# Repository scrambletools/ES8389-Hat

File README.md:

# Scramble Hat-trik — ES8389 Audio Codec HAT

A compact 4-layer audio I/O HAT that stacks on a Waveshare **ESP32-P4** carrier and
gives it a studio-style balanced input and a headset/line output, bridged to the host
over **I²S** (audio) and **I²C** (control). Its headline trick: it taps the carrier's
**802.3 PoE** rail to generate switchable **~48 V-class phantom power** for condenser
microphones — no separate supply.

> **Target carrier:** a Waveshare ESP32-P4-ETH board with PoE module. You will need to solder taps on the output of the bridge rectifiers of the PoE module and connect those wires to J5 on the hat.

---

## Capabilities

- **Balanced analog input** — Neutrik **XLR / ¼″ (6.35 mm) combo** jack (J1) into the
  ES8389 ADC, with input coupling and ESD protection.
- **PoE-tapped phantom power** — ~48 V phantom (tracks the 46–57 V PoE rail) through the
  standard 6.81 kΩ feed pair, **manually switched** (SW1) and **opto-isolated**, with a
  **white presence LED**, a resettable polyfuse, and a TVS rail clamp.
- **Headset / line output** — 3.5 mm **TRRS** jack (J2): stereo output from the DAC plus
  an **electret mic-bias** input path.
- **Stereo audio codec** — Everest **ES8389** (QFN-24): I²S/PCM audio + I²C control.
- **Clean analog power** — ultra-low-noise LDO (TPS7A2033) and ferrite-isolated AVDD.
- **Isolation barrier** — the phantom / XLR side (PGND) is kept separate from the carrier
  audio ground (AGND), bridged only by a **2.2 nF Y2 safety cap** (C19), with a DNP 0 Ω
  ground-lift option (R14).
- **External display header** — 4-pin **I²C** breakout (J6: 3V3 / GND / SDA / SCL) for an
  off-board display.
- **Manufacturable** — JLCPCB gerbers, drills, BOM and placement files are checked in;
  most parts are machine-assembled.

## Signal & power flow

```
  XLR / 6.35" combo (J1) ──coupling──▶ ES8389 ADC ──▶ I²S ──▶ ESP32-P4 carrier
         ▲ phantom
  PoE (J5) ─F1─▶ SW1 ─opto OK1─▶ P-FET Q1 ─▶ 6.81k feed ─▶ XLR pins 2 & 3

  ESP32-P4 carrier ──▶ I²S ──▶ ES8389 DAC ──coupling──▶ TRRS out (J2)
  ESP32-P4 carrier ◀──▶ I²C ◀──▶ ES8389        (+ external display header J6)
```

## Connectors & controls

| Ref | Part | Function |
|---|---|---|
| **J1** | Neutrik NCJ6FA-H | XLR / ¼″ combo — balanced mic/line **input**; ¼″ side is a Hi-Z **instrument input** with auto-detect *(hand-solder)* |
| **J2** | CUI SJ-3524 TRRS | 3.5 mm headset — stereo **output** + electret mic *(hand-solder)* |
| **J3, J4** | 1×7 sockets (8.5 mm) | mezzanine to the carrier — I²S, I²C, power |
| **J5** | 1×2 header | **PoE** rail input from the carrier's PoE module *(hand-solder)* |
| **J6** | 1×4 header | external **I²C** display (3V3 / GND / SDA / SCL) — *DNP; hand-fit (top side) only for a display harness. Eurorack builds don't need it: the interposer drives the display directly* |
| **SW1** | SPDT slide | **phantom power** on/off (manual) — *DNP; populate only in builds that use phantom.* Unpopulated = phantom permanently off; for switchless always-on phantom, bridge SW1 pads 1–2 instead |

## Key components

| Ref | Part | Role |
|---|---|---|
| **U1** | Everest ES8389 (QFN-24) | stereo audio codec |
| **U2** | TI TPS7A2033 | ultra-low-noise 3.3 V analog LDO |
| **OK1** | Everlight EL3H7 (80 V) | opto-isolated phantom enable |
| **Q1** | Vishay Si2325DS | P-FET phantom high-side switch |
| **F1** | 100 mA / 60 V PPTC | phantom / PoE overcurrent protection |
| **D6** | SMBJ58CA TVS | PoE-rail clamp |
| **D8** | white LED | phantom-present indicator |
| **C19** | 2.2 nF Y2 | isolation-barrier safety cap |

## Board

- **≈ 51.4 × 21.1 mm**, **4-layer** (F.Cu / In1.Cu / In2.Cu / B.Cu), 1.6 mm.
- Components on **both sides** (SMD top + bottom) plus a few through-hole connectors.
- Mechanical CAD (enclosure, mounting brackets, faceplates) is maintained outside this repo.

## Host integration

The codec carries audio over **I²S** and is controlled over **I²C**. Its I²C address is
set by the AD0/AD1 straps (R3/R4); R1/R2 are the SDA/SCL pull-ups. Typical firmware is
**ESPHome** or **ESP-ADF** configured for an external I²S codec.

## Mezzanine pinout (J3 / J4)

The header assignment is chosen so **one unmodified board works on two
hosts**: the Waveshare ESP32-P4-ETH carrier it was designed for, and a
**Raspberry Pi Pico** — the hat's footprint (2.54 mm pitch, ~17.8 mm row
spacing, 51 × 21 mm outline) lands exactly on the Pico's USB-end pins
1–7 / 40–34.

| J3 pad | net | P4-ETH | Pico | | J4 pad | net | P4-ETH | Pico |
|---|---|---|---|---|---|---|---|---|
| 1 | `SDA` | GPIO54 | GP0 | | 1 | `+5V` | VCC1_5V | VBUS |
| 2 | `SCL` | GPIO19 | GP1 | | 2 | *pass* | VCC_5V | VSYS |
| 3 | `AGND` | GND | GND | | 3 | `AGND` | GND | GND |
| 4 | `DSDIN` | GPIO18 | GP2 | | 4 | *pass* | 3V3_EN | 3V3_EN |
| 5 | `BCLK` | GPIO17 | GP3 | | 5 | `+3V3` | 3V3 | 3V3(OUT) |
| 6 | `LRCK` | GPIO16 | GP4 | | 6 | `MCLK` | GPIO20 | ADC_VREF — unused |
| 7 | `ASDOUT` | GPIO15 | GP5 | | 7 | `DET` | GPIO21 | GP28 |

Why it lands this way:

- **BCLK/LRCK adjacent** (GP3/GP4, WS = BCLK + 1) — stock side-set PIO
  I²S implementations work unmodified on the Pico.
- **SDA/SCL on GP0/GP1** — a hardware I²C0 pair and MicroPython's default.
- **MCLK sits over the Pico's ADC_VREF**, which is harmless: both ends are
  passive (ADC_VREF is a filtered rail, the codec's MCLK is a hi-Z input),
  so a full 40-pin header can be fitted. The Pico runs the ES8389 in
  **SCLK-source mode** (reg 0x02 bit 6 = 0 — the codec clocks itself from
  BCLK; supported combos cover 44.1 k/48 k at 16/32-bit). The P4 keeps a
  true MCLK on GPIO20. Never jumper a Pico GPIO into a fitted J4.6.
  **R28** (0 Ω 0805, fitted by default) sits in series right at J4.6:
  lift it on a Pico build that uses the Pico's own ADC, so the hat's MCLK
  trace can't couple noise into ADC_VREF — or use its codec-side pad as
  the MCLK injection point for an advanced Pico build (192 kHz needs a
  real MCLK).
- **DET on GP28** — instrument auto-detect readback works on both hosts.

Pico caveats: `+5V` is VBUS, so the analog LDO only runs on USB power;
**phantom power is unavailable** (no PoE front end — see the phantom
section below); full-duplex I²S needs a custom PIO RX machine against
the TX clocks; no ES8389 driver exists for the Pico yet (port from
ESP-ADF or the mainline Linux `es8389.c`). For low BCLK jitter set
`sys_clk` to 153.6 MHz so 3.072 MHz divides exactly.

## Power & host-connection notes

- **USB-C and PoE at the same time is safe.** The carrier has an onboard
  power mux (PoE-priority P-FET + Schottky), so the supplies never fight
  and the PC's USB port can't be back-driven; the 48 V PoE line side stays
  behind the PoE module's transformer isolation (Y-cap bridge only), with
  or without phantom switched on. Flashing/serial over USB while running
  on PoE is the intended debug workflow.
- **Don't hot-plug USB mid-recording** — the ground-equalization transient
  can print as a pop at +36 dB mic gain. Connect first, then record.
- **Bench use on USB only:** leave phantom off (SW1 open/unpopulated) —
  with phantom on, K1/K2 close and reconnect the unpowered PoE module,
  which injects mains hum into the input.
- **Eurorack builds:** USB-C for flashing/serial works while Synthia
  powers the carrier from the rack — the interposer feeds the carrier's
  pre-mux node (bench-verified), so the same USB power mux applies. Avoid
  leaving USB plugged in with the rack powered off (it back-feeds the
  module's buck output); details in the Synthia repo.

## Phantom power source (the PoE tap)

Phantom power is the one hat feature that needs more than the mezzanine:
the 48 V-class rail is **tapped from the PoE bus** and enters the hat on
**J5** (pin 1 = `TAP_HV` +, pin 2 = `TAP_GND` −). On the ESP32-P4-ETH
carrier, the RJ45 mag-jack's pair centre taps run raw to the H7 header;
the **plug-in PoE module** on H7 carries the bridge rectifiers (BD1/BD2)
that turn them into 37–57 V DC before its isolated DC-DC makes the 5 V.
**Tap the two bridge-rectifier outputs on the PoE module** — `+` to
J5.1, `−` to J5.2. The module has **no connector for the tap**, so the
two leads are hand-soldered directly to the rectifier output pins; keep
them reasonably short:

- The tap sits **before** the module's isolation barrier: 37–57 V is
  present whenever a PoE switch/injector is attached, even with SW1 off.
- **Never add bulk capacitance to the tap** (> 0.15 µF breaks the
  module's 802.3af detection signature and the carrier won't power up).
  The hat is designed for this — its reservoir sits after Q1.
- Verify `+`/`−` with a meter at the bridge outputs before wiring; a
  reversed tap defeats the D6/Q1 protection.
- **Raspberry Pi Pico builds: phantom power is unavailable.** A Pico has
  no Ethernet, so nothing like this PoE front end exists — the XLR
  condenser path is dead unless you feed J5 from an equivalent
  **isolated** 44–57 V source with the same polarity. Every other hat
  function (instrument input, dynamic mics, headphone/line out, display)
  works normally on a Pico.

## Microphone setups

Two validated configurations, using the AVB endpoint firmware's controls
(ES8389 PGA via the entity's Mic Gain control; digital gain via the talker's
`ESP_AVB_TALKER_MIC_DIGITAL_GAIN_DB` Kconfig, which also engages an always-on
DC-block ahead of the gain):

| | Condenser (phantom) | Dynamic |
|---|---|---|
| Phantom switch (SW1) | ON | OFF |
| PoE feed (J5) | connected + powered | **disconnect the PoE module** (see note) |
| ES8389 PGA gain | +36 dB | +36 dB (ceiling is +36.5 dB) |
| Digital gain (Kconfig) | 0 dB | **+20 dB** |

Notes:

- **Unpowered PoE module injects mains hum.** With the PoE module installed but
  not powered, the input picks up ~60 Hz mains at near full scale even with SW1
  off — remove/disconnect the module (J5 feed) when running without PoE.
  *(Addressed in the current design: SW1 off now opens both PoE-tap lines
  through the K1/K2 PhotoMOS relays, so the module can stay connected.)*
- Dynamic microphones sit ~20–30 dB below condenser output; the ES8389 PGA
  ceiling (+36.5 dB) alone leaves them ~-40 dBFS, hence the digital gain stage.
- Mic Gain writes above the PGA ceiling **clamp silently** — verify the value
  the response reports, not the value requested.
- The input is wired differential (MIC1P/1N) at the codec; both mic types run
  balanced through the XLR.

## Instrument (guitar) input

The ¼″ side of J1 feeds a high-impedance buffer (U3, ~500 kΩ input) into the
codec's MIC1 channel through an analog mux (U4). Inserting a **mono TS plug**
(guitar cable) shorts the jack's Ring contact to the Sleeve, pulling the
`DET` line low — this automatically switches MIC1 from the XLR mic path to
the buffered instrument path, and is readable by the carrier on **J4.7**
(input, active-low = instrument present). Remove the plug (or use an XLR
mic) and the input returns to the mic path. Phantom power never reaches the
¼″ contacts.

**Hardwiring a guitar without installing the Neutrik connector** — three
connections on the J1 footprint, not two:

| Guitar wire | Pad | Note |
|---|---|---|
| Tip (signal) | either **T** pad | the two T holes are the same net (`GTIP`); one is enough |
| Sleeve (ground) | **S** pad | `PGND`; the larger **G** pad is the same net if a thicker wire is used |
| — | jumper **R → S** | **required.** With no jack fitted, nothing shorts Ring to Sleeve, so `DET` stays high and the mux stays on the (absent) XLR path — the guitar would be silent. The jumper forces instrument mode. Easiest form: populate **R27** (0805 0 Ω, DNP by default) — it shorts `DET` to `PGND` on-board. Remove/leave it off if the Neutrik is fitted. |

**Eurorack module link (J7):** instead of hand-wiring, an optional 1×4
female socket **J7** (8.5 mm stacking, same series as J3/J4, DNP by
default) direct-mates the **Synthia** eurorack interposer's J8 header. Populate J7
**only when J1 is absent** (they use the same input path), and populate
**R27** with it (the module's input jack can't pull `DET` low). Pinout:
1 = `GTIP`, 2 = `PGND`, 3 = `AGND`, 4 = `HP_L_OUT` — signals on the outer
pins with both grounds between them.

**Eurorack + display:** the interposer drives a display directly from its
own display socket (J10, on the main GND/3V3/I²C nets), so **J6 can stay
DNP in eurorack builds** — no bottom-side fitting needed. Fit J6 (top
side) only for a normal display harness in non-rack builds.

**Cable:** use two-core shielded cable (the input is high impedance and
hums otherwise) — one core to **T** (signal), the other core to **S**
(return), and the **shield joined to S at the hat end only**; at the guitar
end connect just the two cores (tip / sleeve) and trim + insulate the
shield. The return current then flows in the tightly-coupled core pair
while the shield does pure screening — bonding it at both ends would let
ground-loop and pickup currents flow through it in series with the signal.
For very short runs (a few cm) plain coax — center to T, shield as the
return to S, connected at both ends — also works.

## Mono amplifier output (hardwiring J2)

To feed a mono amplifier that expects only tip and sleeve, skip the 3.5 mm jack
and solder wires directly to the J2 footprint. **Careful:** J2 is wired as a
**CTIA TRRS** headset jack, so the pad named `S` is *not* ground — on CTIA the
physical sleeve is the microphone conductor.

| Amp wire | Pad | Note |
|---|---|---|
| Tip (signal) | **T** | `HP_L_OUT` — left audio channel |
| Sleeve (ground) | **TN** | `AGND` — audio ground. **Do not use the `S` pad**: it is the headset-mic line (`MIC2_RAW`) and carries mic bias — grounding it gives hum and injects into the MIC2 input. |

Notes:

- This taps the **left channel only**; have firmware output a mono downmix if
  the source is stereo. Do **not** bridge the `T` and `R` pads to "sum" the
  channels — that shorts the two DAC output stages into each other. (A passive
  sum, if ever wanted, is a ~1 kΩ resistor from each of T and R into the amp
  tip.)
- An amp input (typically ≥10 kΩ) is a much lighter load than headphones, so
  the 22 µF output coupling caps give essentially full bass extension here.
- Unlike the J1 guitar hardwire, **no jumper is required** — J2 has no
  plug-detect circuit.
- **Cable:** use two-core shielded cable — one core to **T** (signal), the
  other core to **TN** (return), **shield joined to TN at the hat end
  only**; at the amp end connect just the two cores (tip / sleeve) and
  trim + insulate the shield. This keeps the shield free of audio and
  ground-loop current (which its resistance would otherwise convert to hum
  in series with the signal) while still screening the run. This link is
  forgiving (low-Z source into a ≥10 kΩ amp input), so for runs under
  ~10 cm plain coax with the shield as the return, connected at both ends,
  is also fine.

## Repository layout

| Path | Contents |
|---|---|
| `scramble_hat.kicad_sch` / `.kicad_pcb` | hierarchical schematic + layout |
| `BOM.csv` | bill of materials — **single source of truth** |
| `fab/` | JLCPCB gerbers, drills, BOM, CPL — see [`fab/README.md`](fab/README.md) |
| `tools/gen_fab.py` | regenerate every production file from the design |
| `tools/check_sync.py` | verify schematic ↔ PCB netlist agreement |
| `lib/` | project symbols, footprints, 3D models |
| `docs/` | schematic + silkscreen PDFs |

## Manufacturing

See **[`fab/README.md`](fab/README.md)** for the full ordering guide. In short: JLCPCB
fabricates and assembles most parts; you **hand-solder J1, J2, J5 and C19** (the Y-cap),
and **R14 is left unpopulated** (DNP ground-lift jumper). **J6** (display header) is also
DNP — hand-fit it only when a display is used (top side normally, bottom side for the
eurorack stack). Regenerate all fab outputs with:

```sh
python3 tools/gen_fab.py
```

> ⚠️ Before committing an assembly order, verify part rotations in JLCPCB's preview —
> especially **U1** (the QFN's rotation is applied manually and is a best estimate).

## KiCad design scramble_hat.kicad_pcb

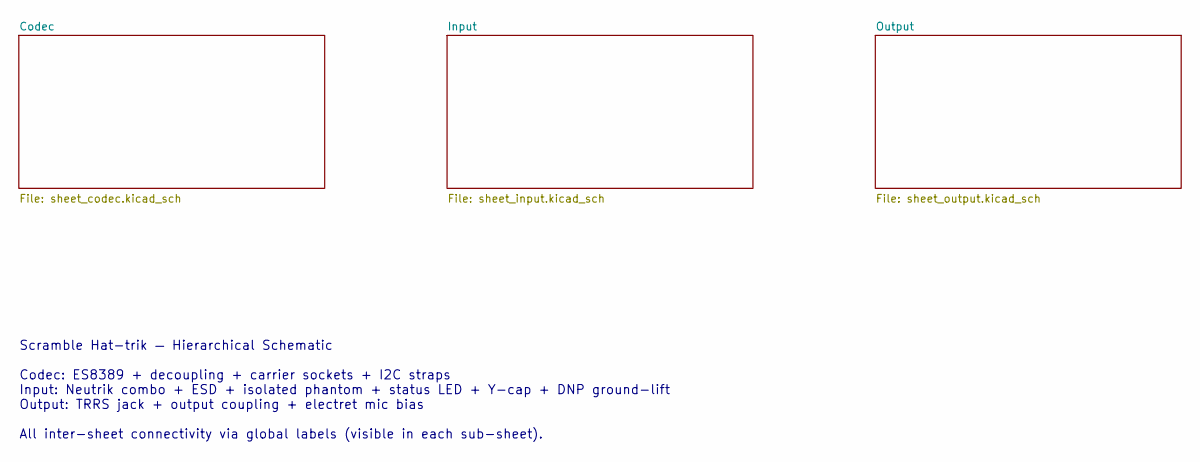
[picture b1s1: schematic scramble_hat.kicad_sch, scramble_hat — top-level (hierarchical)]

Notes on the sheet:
Scramble Hat-trik — Hierarchical Schematic Codec: ES8389 + decoupling + carrier sockets + I2C straps Input: Neutrik combo + ESD + isolated phantom + status LED + Y-cap + DNP ground-lift Output: TRRS jack + output coupling + electret mic bias All inter-sheet connectivity via global labels (visible i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

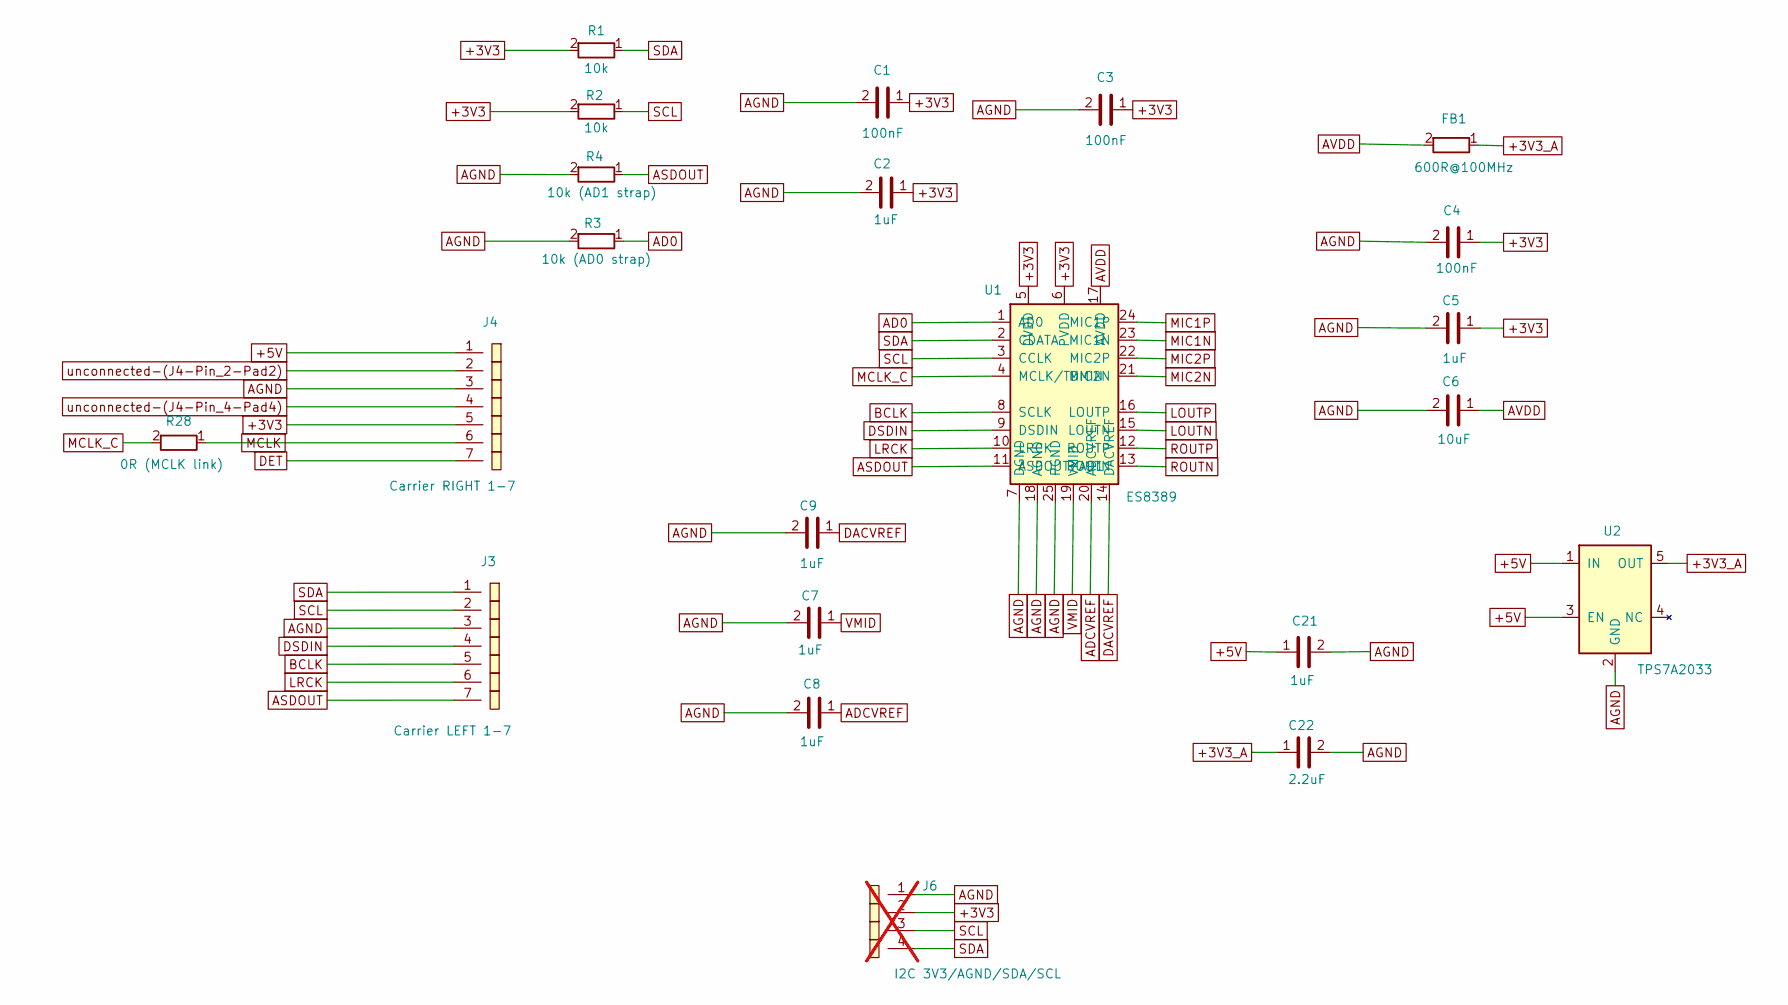
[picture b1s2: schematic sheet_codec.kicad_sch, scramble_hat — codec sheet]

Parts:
C1, C3, C4: 100nF; C_0402_1005Metric
C2, C5, C7, C8, C9, C21: 1uF; C_0402_1005Metric
C6: 10uF; C_0805_2012Metric
C22: 2.2uF; C_0402_1005Metric
FB1: 600R@100MHz; L_0603_1608Metric
J3: Carrier LEFT 1-7; PinSocket_1x07_P2.54mm_Vertical
J4: Carrier RIGHT 1-7; PinSocket_1x07_P2.54mm_Vertical
J6: I2C 3V3/AGND/SDA/SCL; PinHeader_1x04_P2.54mm_Vertical; not fitted
R1, R2: 10k; R_0402_1005Metric
R3: 10k (AD0 strap); R_0402_1005Metric
R4: 10k (AD1 strap); R_0402_1005Metric
R28: 0R (MCLK link); R_0805_2012Metric
U1: ES8389; ES8389_QFN24_P0.35mm
U2: TPS7A2033; SOT-23-5

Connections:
+3V3: C1.1, C2.1, C3.1, C4.1, C5.1, J4.5, J6.2, R1.2, R2.2, U1.5 (DVDD), U1.6 (PVDD); also elsewhere on the board
+3V3_A: C22.1, FB1.1, U2.5 (OUT)
+5V: C21.1, J4.1, U2.1 (IN), U2.3 (EN); also elsewhere on the board
AD0: R3.1, U1.1 (AD0)
ADCVREF: C8.1, U1.20 (ADCVREF)
AGND: C1.2, C2.2, C3.2, C4.2, C5.2, C6.2, C7.2, C8.2, C9.2, C21.2, C22.2, J3.3, J4.3, J6.1, R3.2, R4.2, U1.7 (DGND), U1.18 (AGND), U1.25 (PGND), U2.2 (GND); also elsewhere on the board
ASDOUT: J3.7, R4.1, U1.11 (ASDOUT/AD1)
AVDD: C6.1, FB1.2, U1.17 (AVDD); also elsewhere on the board
BCLK: J3.5, U1.8 (SCLK)
DACVREF: C9.1, U1.14 (DACVREF)
DET: J4.7; also elsewhere on the board
DSDIN: J3.4, U1.9 (DSDIN)
LOUTN: U1.15 (LOUTN)
LOUTP: U1.16 (LOUTP); also elsewhere on the board
LRCK: J3.6, U1.10 (LRCK)
MCLK: J4.6, R28.1
MCLK_C: R28.2, U1.4 (MCLK/TDMIN)
MIC1N: U1.23 (MIC1N); also elsewhere on the board
MIC1P: U1.24 (MIC1P); also elsewhere on the board
MIC2N: U1.21 (MIC2N); also elsewhere on the board
MIC2P: U1.22 (MIC2P); also elsewhere on the board
ROUTN: U1.13 (ROUTN)
ROUTP: U1.12 (ROUTP); also elsewhere on the board
SCL: J3.2, J6.3, R2.1, U1.3 (CCLK)
SDA: J3.1, J6.4, R1.1, U1.2 (CDATA)
VMID: C7.1, U1.19 (VMID)

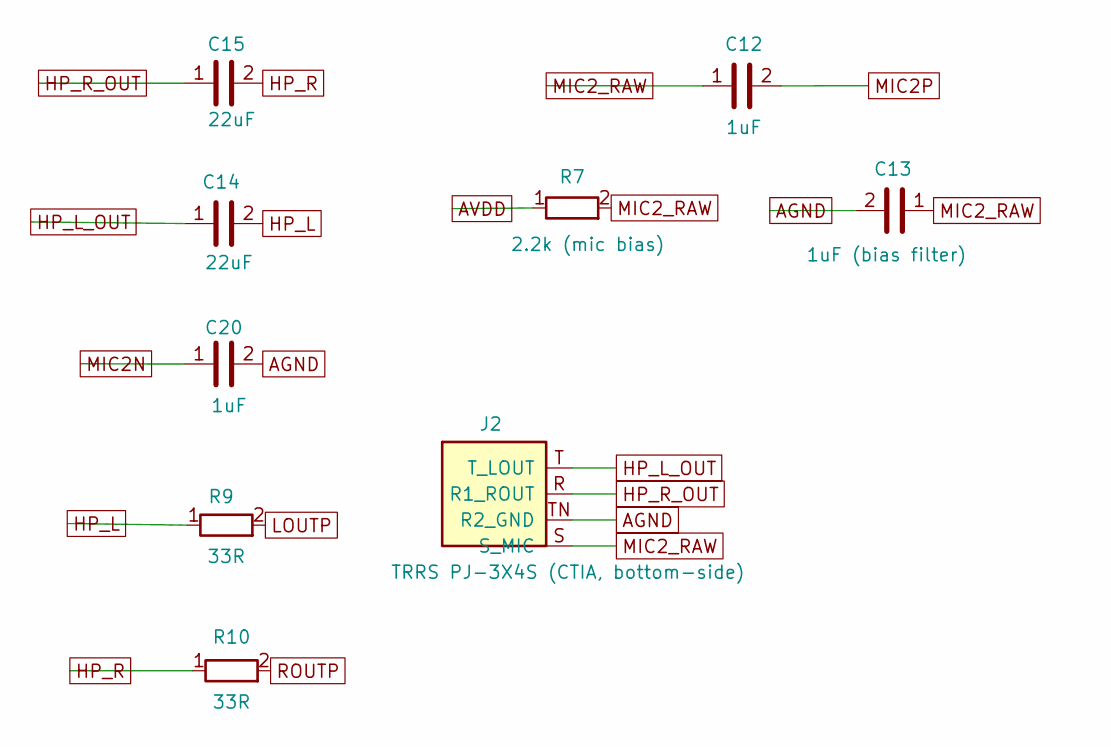
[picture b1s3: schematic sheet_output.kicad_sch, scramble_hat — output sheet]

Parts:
C12, C20: 1uF; C_0402_1005Metric
C13: 1uF (bias filter); C_0402_1005Metric
C14, C15: 22uF; C_0805_2012Metric
J2: TRRS PJ-3X4S (CTIA, bottom-side); Jack_3.5mm_CUI_SJ-3524-SMT_Horizontal
R7: 2.2k (mic bias); R_0402_1005Metric
R9, R10: 33R; R_0402_1005Metric

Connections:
AGND: C13.2, C20.2, J2.TN (R2_GND); also elsewhere on the board
AVDD: R7.1; also elsewhere on the board
HP_L: C14.2, R9.1
HP_L_OUT: C14.1, J2.T (T_LOUT); also elsewhere on the board
HP_R: C15.2, R10.1
HP_R_OUT: C15.1, J2.R (R1_ROUT)
LOUTP: R9.2; also elsewhere on the board
MIC2N: C20.1; also elsewhere on the board
MIC2P: C12.2; also elsewhere on the board
MIC2_RAW: C12.1, C13.1, J2.S (S_MIC), R7.2
ROUTP: R10.2; also elsewhere on the board

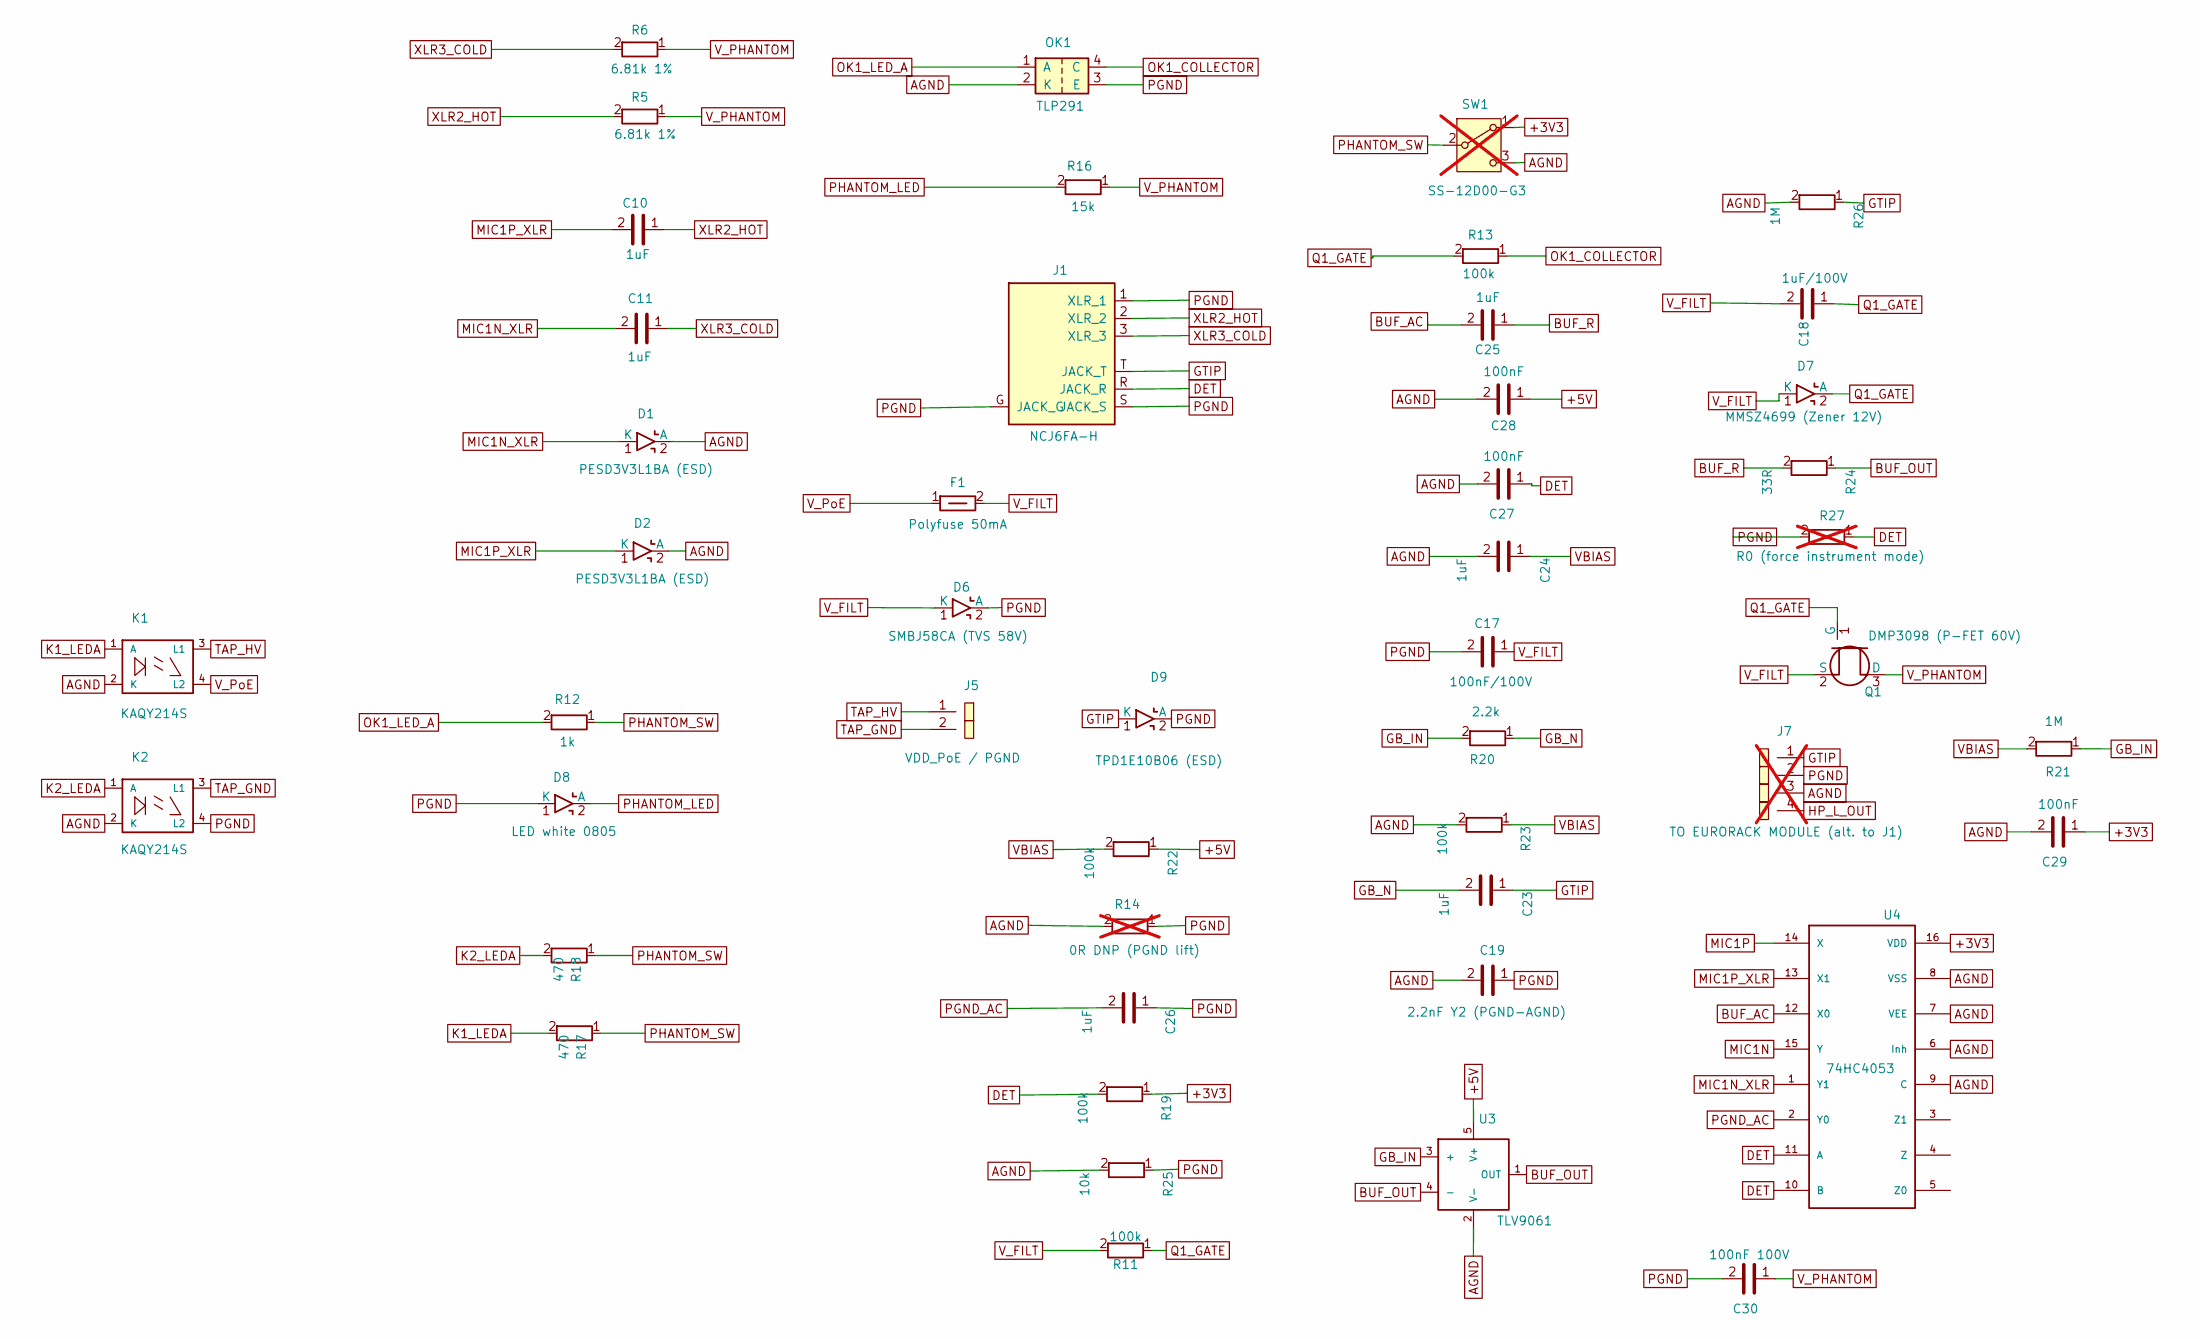
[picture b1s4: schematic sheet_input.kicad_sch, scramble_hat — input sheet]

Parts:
C10, C11: 1uF; C_0805_2012Metric
C17: 100nF/100V; C_0805_2012Metric
C18: 1uF/100V; C_1206_3216Metric
C19: 2.2nF Y2 (PGND-AGND); C_Y2_DE2B_TH
C23, C24, C25, C26: 1uF; C_0402_1005Metric
C27, C28, C29: 100nF; C_0402_1005Metric
C30: 100nF 100V; C_0805_2012Metric
D1, D2: PESD3V3L1BA (ESD); D_SOD-323
D6: SMBJ58CA (TVS 58V); D_SMA
D7: MMSZ4699 (Zener 12V); D_SOD-123
D8: LED white 0805; LED_0805_2012Metric
D9: TPD1E10B06 (ESD); Texas_DPY0002A_0.6x1mm_P0.65mm
F1: Polyfuse 50mA; Fuse_1812_4532Metric
J1: NCJ6FA-H; Jack_XLR-6.35mm_Neutrik_NCJ6FA-H_Horizontal
J5: VDD_PoE / PGND; PinHeader_1x02_P2.54mm_Vertical
J7: TO EURORACK MODULE (alt. to J1); PinSocket_1x04_P2.54mm_Vertical; not fitted
K1, K2: KAQY214S; SOP-4_3.8x4.1mm_P2.54mm
OK1: TLP291; SOP-4_4.4x2.6mm_P1.27mm
Q1: DMP3098 (P-FET 60V); SOT-23
R5, R6: 6.81k 1%; R_0805_2012Metric
R11, R13, R19, R22, R23: 100k; R_0402_1005Metric
R12: 1k; R_0402_1005Metric
R14: 0R DNP (PGND lift); R_0402_1005Metric; not fitted
R16: 15k; R_0805_2012Metric
R17, R18: 470; R_0402_1005Metric
R20: 2.2k; R_0402_1005Metric
R21, R26: 1M; R_0402_1005Metric
R24: 33R; R_0402_1005Metric
R25: 10k; R_0402_1005Metric
R27: R0 (force instrument mode); R_0805_2012Metric; not fitted
SW1: SS-12D00-G3; SW_Slide_SS-12D00-G3; not fitted
U3: TLV9061; SOT-23-5
U4: 74HC4053; TSSOP-16_4.4x5mm_P0.65mm

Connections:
+3V3: C29.1, R19.1, SW1.1 (A), U4.16 (VDD); also elsewhere on the board
+5V: C28.1, R22.1, U3.5 (V+); also elsewhere on the board
AGND: C19.2, C24.2, C27.2, C28.2, C29.2, D1.2 (A), D2.2 (A), J7.3, K1.2 (K), K2.2 (K), OK1.2 (K), R14.2, R23.2, R25.2, R26.2, SW1.3 (C), U3.2 (V-), U4.6 (Inh), U4.7 (VEE), U4.8 (VSS), U4.9 (C); also elsewhere on the board
BUF_AC: C25.2, U4.12 (X0)
BUF_OUT: R24.1, U3.1 (OUT), U3.4 (-)
BUF_R: C25.1, R24.2
DET: C27.1, J1.R (JACK_R), R19.2, R27.1, U4.10 (B), U4.11 (A); also elsewhere on the board
GB_IN: R20.2, R21.1, U3.3 (+)
GB_N: C23.2, R20.1
GTIP: C23.1, D9.1 (K), J1.T (JACK_T), J7.1, R26.1
HP_L_OUT: J7.4; also elsewhere on the board
K1_LEDA: K1.1 (A), R17.2
K2_LEDA: K2.1 (A), R18.2
MIC1N: U4.15 (Y); also elsewhere on the board
MIC1N_XLR: C11.2, D1.1 (K), U4.1 (Y1)
MIC1P: U4.14 (X); also elsewhere on the board
MIC1P_XLR: C10.2, D2.1 (K), U4.13 (X1)
OK1_COLLECTOR: OK1.4 (C), R13.1
OK1_LED_A: OK1.1 (A), R12.2
PGND: C17.2, C19.1, C26.1, C30.2, D6.2 (A), D8.1 (K), D9.2 (A), J1.1 (XLR_1), J1.G (JACK_G), J1.S (JACK_S), J7.2, K2.4 (L2), OK1.3 (E), R14.1, R25.1, R27.2
PGND_AC: C26.2, U4.2 (Y0)
PHANTOM_LED: D8.2 (A), R16.2
PHANTOM_SW: R12.1, R17.1, R18.1, SW1.2 (B)
Q1_GATE: C18.1, D7.2 (A), Q1.1 (G), R11.1, R13.2
TAP_GND: J5.2, K2.3 (L1)
TAP_HV: J5.1, K1.3 (L1)
VBIAS: C24.1, R21.2, R22.2, R23.1
V_FILT: C17.1, C18.2, D6.1 (K), D7.1 (K), F1.2, Q1.2 (S), R11.2
V_PHANTOM: C30.1, Q1.3 (D), R5.1, R6.1, R16.1
V_PoE: F1.1, K1.4 (L2)
XLR2_HOT: C10.1, J1.2 (XLR_2), R5.2
XLR3_COLD: C11.1, J1.3 (XLR_3), R6.2

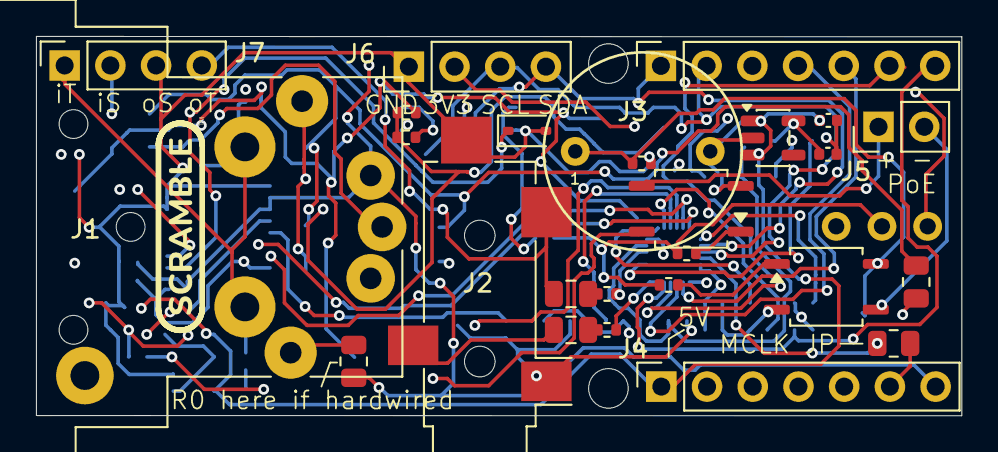
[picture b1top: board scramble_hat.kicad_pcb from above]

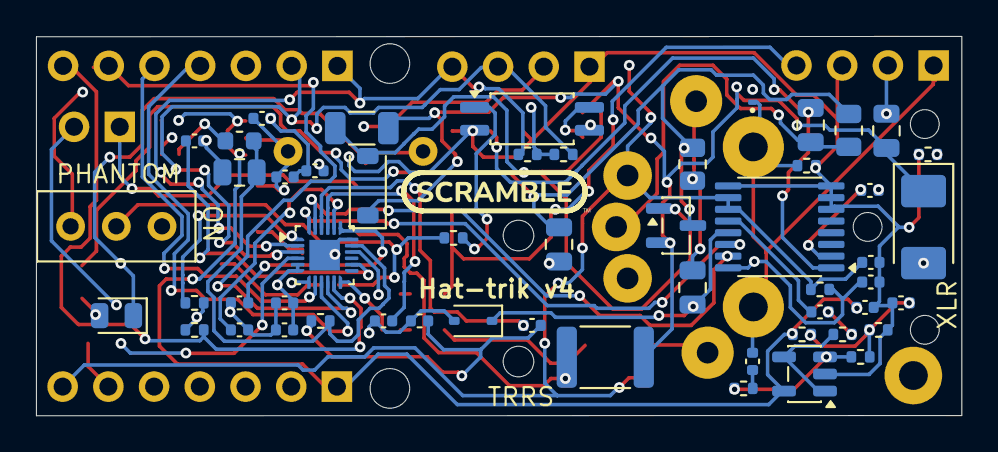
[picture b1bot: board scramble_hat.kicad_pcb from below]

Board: 4 copper layers, 51.4 x 21.1 mm, 79 parts (53 on the bottom side), 54 nets.

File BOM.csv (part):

Comment,Designator,Qty,MPN,Manufacturer,Footprint,LCSC Part #,JLCPCB Class,Mount,DNP,Unit Price USD,Notes,Datasheet
ES8389 audio codec,U1,1,ES8389,Everest Semi,QFN-24 3x3 P0.35mm,C22380673,Extended,SMT,,0.712,Custom 0.35mm-pitch footprint (scramble_hat lib),https://datasheet.lcsc.com/datasheet/pdf/4ae5a2e8327541a33b0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
Ultra-low-noise LDO 3.3V,U2,1,TPS7A2033PDBVR,Texas Instruments,SOT-23-5,C2862740,Extended,SMT,,0.2102,AVDD analog LDO; +5V -> +3V3_A,https://datasheet.lcsc.com/datasheet/pdf/e9493c53ea71c523359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
Optocoupler 80V,OK1,1,EL3H7(C)(TA)-VG,Everlight,SOP-4-1.27mm,C17549577,Extended,SMT,,0.0741,"PHANTOM_EN isolation; 80V Vceo; SOP-4 1.27mm half-pitch; pinout 1=A 2=K 3=E 4=C. Same die/package/CTR-bin as EL3H7(C)(TA)-G (C92243, went stock-0 2026-07-26); -VG = halogen-free packing. CTR 200-400%.",https://www.everlighteurope.com/custom/files/datasheets/DPC-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
P-MOSFET 150V,Q1,1,Si2325DS-T1-GE3,Vishay,SOT-23,C60773,Extended,SMT,,0.4946,Phantom switch; gate clamped by D7,https://datasheet.lcsc.com/datasheet/pdf/8db77570eae4643cba5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
"ESD diode, 3.3V bidir","D1, D2",2,PESD3V3L1BA-N,BORN,SOD-323,C316020,Extended,SMT,,0.0611,Mic-line ESD (was 4-line PESD3V3L4UG/C70500 using 1 of 4 channels). Bidirectional 2-pin: no polarity/rotation. Saves ~$0.14/board,https://datasheet.lcsc.com/datasheet/pdf/a036bfae0471726dc4b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
TVS 58V 600W bidir,D6,1,SMBJ58CA,Littelfuse,SMA,C151267,Extended,SMT,,0.121,PoE rail clamp,https://datasheet.lcsc.com/datasheet/pdf/4ab84a227fae39f9eac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
Zener 12V 0.5W,D7,1,MMSZ5242BT1G,onsemi,SOD-123,C82050,Basic/Ext,SMT,,0.0354,Q1 gate clamp,https://datasheet.lcsc.com/datasheet/pdf/03657490163bd8bf585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
"LED, white",D8,1,KT-0805W,Hubei KENTO,0805,C34499,Basic,SMT,,0.0203,Phantom-present indicator (white); KT-0805W Basic in-stock,https://datasheet.lcsc.com/datasheet/pdf/48953f05e6e6e0a517a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
PPTC 100mA hold / 60V,F1,1,1812L010/60DR,Littelfuse,1812,C207062,Extended,SMT,,0.2151,True 1812 (matches board land); 100mA hold/300mA trip. prior 0ZCJ0005FF2E/C194141 is 1206 - wrong size,https://datasheet.lcsc.com/datasheet/pdf/f489f06aaead3504c46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
Ferrite 600R @100MHz,FB1,1,BLM18AG601SN1D,Murata,0603,C19330,Basic/Ext,SMT,,0.0149,AVDD ferrite,https://datasheet.lcsc.com/datasheet/pdf/2d503a4b167da9bb5d0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
100nF 50V X7R,"C1, C3, C4, C27, C28, C29",6,CC0402KRX7R9BB104,Yageo,0402,C131394,Basic,SMT,,0.0157,,https://datasheet.lcsc.com/datasheet/pdf/23ccee80ee542e7cf15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
1uF 25V X5R,"C2, C5, C7, C8, C9, C12, C13, C20, C21, C23, C24, C25, C26",13,CL05A105KA5NQNC,Samsung,0402,C52923,Basic,SMT,,0.0266,,https://datasheet.lcsc.com/datasheet/pdf/02336ea48ea44ca18c7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
10uF 16V X5R,C6,1,GRM21BR61C106KE15L,Murata,0805,C77075,Basic,SMT,,0.0716,AVDD bulk,https://datasheet.lcsc.com/datasheet/pdf/a4d1e2744bd5d44ba57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
1uF 100V X7R,"C10, C11",2,CC0805KKX7R0BB105,Yageo,0805,C5370002,Extended,SMT,,0.1307,XLR coupling (phantom side); 100V for margin,https://datasheet.lcsc.com/datasheet/pdf/23ccee80ee542e7cf15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
22uF 10V X5R,"C14, C15",2,CL21A226MPQNNNE,Samsung,0805,C29277,Extended,SMT,,0.1722,HP coupling,https://datasheet.lcsc.com/datasheet/pdf/02336ea48ea44ca18c7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
100nF 100V X7R,"C17, C30",2,0805B104K101NT,Fenghua,0805,C89258,Extended,SMT,,0.026,C17 = tap-line bridge; C30 = V_PHANTOM bypass at Q1 drain (PoE-converter hash filter; keep OFF the tapped bus - 802.3 detection limit). 100V rating required (57V rail).,https://datasheet.lcsc.com/datasheet/pdf/9f6ef17093b8d551f8b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
1uF 100V X7R,C18,1,CL31B105KCHNNNE,Samsung,1206,C13832,Extended,SMT,,0.1396,Q1 gate soft-start,https://datasheet.lcsc.com/datasheet/pdf/02336ea48ea44ca18c7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
2.2nF Y2 300VAC,C19,1,DE2E3SA222MA3BT02F,Murata,Disc TH 7.5mm,C524537,n/a,TH,DNP,0.087,"Hand-solder by user (Y2 safety cap; NOT JLC-assembled). X1/Y2 300/250VAC 2.2nF 7.5mm disc; source DigiKey/Mouser (Murata DE2E3) or TDK CS11-E2GA222MYNSA equivalent LCSC ALT (in stock 42k, $0.03): Hongzhi Y26F1E222M / C332371, Y2 250VAC 2.2nF P7.5 - same land.",https://datasheet.lcsc.com/datasheet/pdf/d99197b87f9afabff40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
2.2uF 10V X5R,C22,1,CL05A225KP5NSNC,Samsung,0402,C107369,Basic,SMT,,0.0239,LDO output cap,https://datasheet.lcsc.com/datasheet/pdf/02336ea48ea44ca18c7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
10k 1%,"R1, R2, R3, R4, R25",5,RC0402FR-0710KL,Yageo,0402,C60490,Extended,SMT,,0.0059,I2C pullups + AD0/AD1 straps. C# was C25744 = UNI-ROYAL 0402WGF1002TCE (Basic) but now OUT OF STOCK; switched to the matching Yageo MPN C60490 (in stock ~92k). Verify Basic/Extended badge in JLC UI,https://datasheet.lcsc.com/datasheet/pdf/b426be3ce22c6de3e0c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
6.81k 1%,"R5, R6",2,ERJ6ENF6811V,Panasonic,0805,C3025619,Extended,SMT,,0.0082,Phantom feed pair (no JLCPCB Basic for 6.81k 0805),https://datasheet.lcsc.com/datasheet/pdf/ac61a13441f28ab6046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
2.2k 1%,"R7, R20",2,AC0402FR-072K2L,Yageo,0402,C144773,Basic,SMT,,0.0057,Mic bias; C# C25879 stock-0 at LCSC 2026-07-26; swapped to C144773.,https://datasheet.lcsc.com/datasheet/pdf/3511efb0564cb1711d9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
33R 1%,"R9, R10, R24",3,RC0402FR-0733RL,Yageo,0402,C138002,Basic,SMT,,0.0056,HP output series; C# C25105 stock-0 at LCSC 2026-07-26; swapped to C138002.,https://datasheet.lcsc.com/datasheet/pdf/b426be3ce22c6de3e0c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
100k 1%,"R11, R13, R19, R22, R23",5,RC0402FR-07100KL,Yageo,0402,C60491,Basic,SMT,,0.0061,Q1 gate pullup / opto pulldown; C# C25741 stock-0 at LCSC 2026-07-26; swapped to C60491.,https://datasheet.lcsc.com/datasheet/pdf/b426be3ce22c6de3e0c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
1k 1%,R12,1,RC0402FR-071KL,Yageo,0402,C106235,Basic,SMT,,0.0062,Opto LED current limit (switch -> opto); C# C11702 stock-0 at LCSC 2026-07-26; swapped to C106235.,https://datasheet.lcsc.com/datasheet/pdf/b426be3ce22c6de3e0c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
0R,R14,1,RC0402JR-070RL,Yageo,0402,,n/a,DNP,DNP,0.02,Ground-lift jumper - not populated (true DNP),
15k 1% 1/4W,R16,1,AC0805FR-7W15KL,Yageo,0805,C20142753,Extended,SMT,,0.0085,D8 LED current-limit (bright ~3mA); 1/4W anti-surge ~193mW at 57V rail,https://datasheet.lcsc.com/datasheet/pdf/3511efb0564cb1711d9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
XLR / 6.35mm combo jack,J1,1,NCJ6FA-H,Neutrik,TH combo,C368458,n/a,TH,DNP,2.6072,"Hand-solder (TH). Switched combo (A type), ~$1.82 vs FI $4.34; jack switch contacts unused",https://datasheet.lcsc.com/datasheet/pdf/9e398f1fdd271e3584b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
3.5mm TRRS jack,J2,1,SJ-3524-SMT-TR,CUI,SMT,,n/a,SMT,DNP,1.40,"SJ-3524 family OUT OF STOCK at LCSC+JLCPCB (2026-06) - hand-solder from DigiKey 281298 (base -TR, 67k stock; any color variant fits)",https://www.sameskydevices.com/product/interconnect/connecto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
"1x7 female socket, 8.5mm","J3, J4",2,PM254V-11-07-H85,XFCN,PinSocket_1x07_2.54mm TH,C2832270,THT,TH,,0.0976,JLCPCB THT-assembled (enable THT components at checkout); 8.5mm stack height,https://datasheet.lcsc.com/datasheet/pdf/5aa023c30ffb4f60788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
1x2 pin header,J5,1,PRPC002SAAN-RC,Sullins,PinHeader_1x02_2.54mm TH,,n/a,TH,DNP,0.30,PoE module connection - hand-solder,
1x4 pin header,J6,1,B-2100S04P-A110,Ckmtw,PinHeader_1x04_2.54mm TH,C124378,Extended,TH,DNP,0.055,"Hand-fit per build: top side for a display harness, BOTTOM side for the eurorack stack (mates interposer J9). Pinout 1=AGND 2=+3V3 3=SCL 4=SDA",https://datasheet.lcsc.com/datasheet/pdf/219f7e7eb5f34457895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
"1x4 female socket, 8.5mm",J7,1,PM254V-11-04-H85,XFCN,PinSocket_1x04_2.54mm TH,C541851,Extended,TH,DNP,0.0703,OPTIONAL: populate only when J1 is absent; direct-mates eurorack module J8 (same H85 stack series as J3/J4). Pin 1=GTIP 2=PGND 3=AGND 4=HP_L_OUT,https://datasheet.lcsc.com/datasheet/pdf/7912db05a9479e06d28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
0R jumper 0805,R27,1,0805W8F0000T5E,UNI-ROYAL,0805,C17477,Basic,SMT,DNP,0.0101,"OPTIONAL: populate to force instrument mode (DET->PGND, replaces J1 ring-short); required when input arrives via J7",https://datasheet.lcsc.com/datasheet/pdf/0a975aaa49b7c97f38a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
0R jumper 0805,R28,1,0805W8F0000T5E,UNI-ROYAL,0805,C17477,Basic,SMT,,0.0101,"MCLK series link (J4.6 -> codec), fitted by default; lift only on a Pico build that uses the Pico's own ADC (isolates the MCLK trace from ADC_VREF)",https://datasheet.lcsc.com/datasheet/pdf/0a975aaa49b7c97f38a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

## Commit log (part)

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2026-05-31 init: first commit of the hat design
2026-06-19 design: full iteration since init — codec, phantom/PoE, LDO, BOM, fab
    First substantive commit since init; captures the entire design
    iteration and quiets KiCad churn in-repo.
    Codec / PCB
    - ES8389: custom QFN-24 0.35mm land pattern (ES8389_QFN24_P0.35mm)
    - Corrected mirror-reversed codec I2C/I2S pins
    - Un-mirrored all B.Cu footprints that imported un-flipped
2026-06-24 pcb: move D1 clear of J2 TRRS courtyard; refill zones
    D1 (MIC1N ESD, SOT-353) was overlapping the SJ-3524 TRRS jack
    courtyard; relocated to (107.9, 85.9), ~10mm clear of J2. Refilled
    zones so PGND_phantom carves clearance around D1's AGND/MIC1N fan-out
    vias.
    DRC: 0 errors, 0 unconnected, 0 courtyard overlaps.
2026-06-24 fab: regenerate gerbers, drill & CPL for D1 move
    Re-plotted from the DRC-clean board after relocating D1 clear of the
    J2 TRRS courtyard and refilling zones. Updated gerbers (D1 pads, PGND
    zone reflow on In1/B.Cu), drill, gerbers.zip, and CPL (D1 -> 107.899,
    -85.867; all other parts unchanged). BOM unchanged (no part changes).
2026-06-24 lib: replace C19 Y2 cap with available Murata DE2E3SA222MA3BT02F
    Old DE2E3KY222MA3BM02F (LCSC C161048) is EOL/unavailable. Swap to
    DE2-SA series DE2E3SA222MA3BT02F (LCSC C524537) — same 2.2nF 250VAC
    X1/Y2, same 7.5mm-pitch TH land, so footprint is unchanged.
    - BOM.csv: MPN, LCSC#, price (~$0.11@5+), notes
    - C_Y2_DE2B_TH.kicad_mod: descr + datasheet -> Murata DE2-SA PDF
    - PCB embedded footprint descr synced (string-only; no geometry/net/
2026-06-24 lib: add representative 3D model for SW1 (SS-12D00-G3 slide switch)
    The SW_Slide_SS-12D00-G3 footprint had no (model ...) line, so SW1
    showed nothing in the 3D viewer. Add a dimensionally-representative
    VRML model (black body ~8.8x3.9x3.4mm + slider actuator + 3 leads,
    2.54mm pitch) for clearance/height checks.
    - lib/3dmodels/SS-12D00-G3.wrl (new; authored in mm, scale 0.3937 = 1/2.54)
    - SW_Slide_SS-12D00-G3.kicad_mod: (model ...) ref added
2026-06-24 lib: correct SW1 stem dimensions per SS-12D07 datasheet
    SS-12D07-VG/GA/PA datasheet (Documents/Specs) gives the actuator as a
    2.0mm-wide stem (front + side views), not the 2.8x1.6mm flat nub first
    modeled. The actuator height (L / "VG=") is left blank as the variant
    dimension; set stem protrusion to 3.0mm per visual proportion (~80-90%
    of body height). Stem now: 2.0 x 2.0mm square post + 0.4mm notched tip.
    Verified via kicad-cli pcb render.
2026-06-24 lib: convert SW1 switch model to STEP (unity scale) for STEP export
    KiCad's STEP exporter only embeds STEP/IGES models and warns on
    non-unity scaled models. The SW1 model was VRML referenced at scale
    0.3937 (VRML's 2.54mm-unit workaround), which triggered the
    "non-unity scaled model may produce unreliable results" warning and
    left the switch out of the STEP.
    Replace the .wrl with a hand-generated STEP B-rep (mm, same geometry:
